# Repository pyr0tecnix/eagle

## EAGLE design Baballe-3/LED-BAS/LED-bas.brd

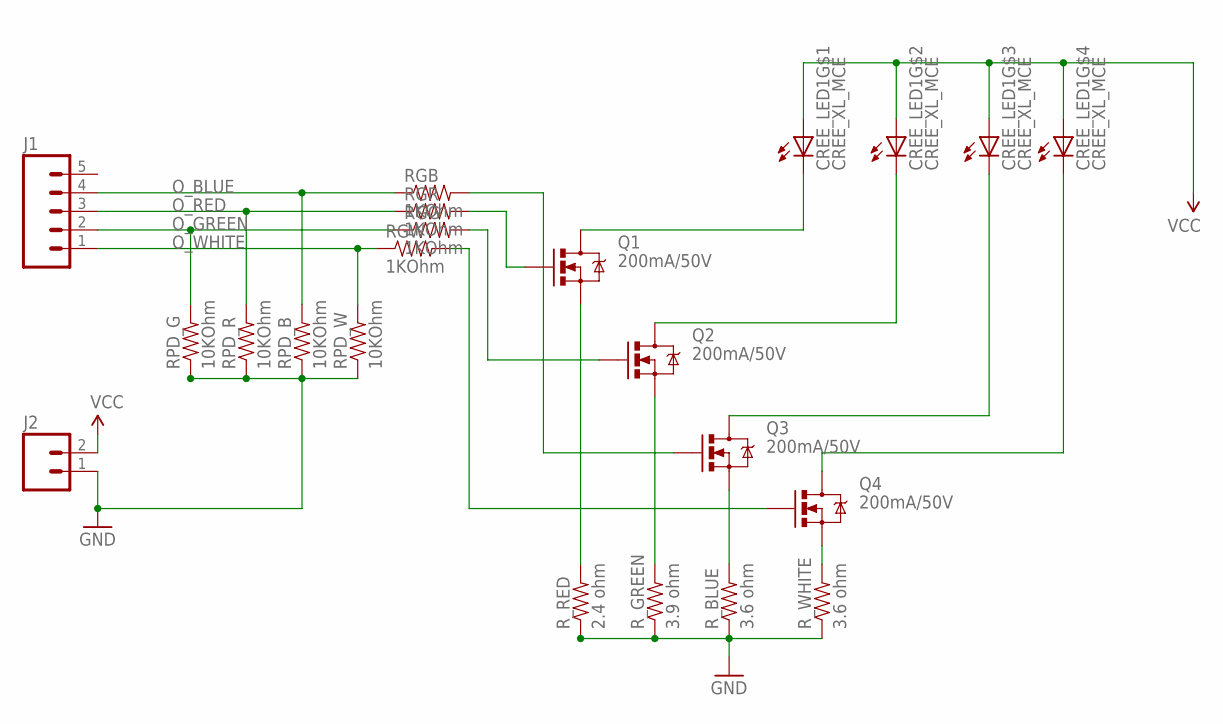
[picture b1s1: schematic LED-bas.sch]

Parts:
CREE_LED1: CREE_XL_MCE
J1: M05NO_SILK; 1X05_NO_SILK
J2: M021X02_NO_SILK; 1X02_NO_SILK
Q1, Q2, Q3, Q4: 200mA/50V; SOT23-3
RGB: 1KOhm; 0805
RGG: 1KOhm; 0805
RGR: 1KOhm; 0805
RGW: 1KOhm; 0805
RPD_B: 10KOhm; 0805
RPD_G: 10KOhm; 0805
RPD_R: 10KOhm; 0805
RPD_W: 10KOhm; 0805
R_BLUE: 3.6 ohm; 0805
R_GREEN: 3.9 ohm; 0805
R_RED: 2.4 ohm; 0805
R_WHITE: 3.6 ohm; 0805

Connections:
GND: J2.1, RPD_B.1, RPD_G.1, RPD_R.1, RPD_W.1, R_BLUE.1, R_GREEN.1, R_RED.1, R_WHITE.1
unnamed: Q3.2 (S), R_BLUE.2
unnamed: Q2.2 (S), R_GREEN.2
unnamed: Q1.2 (S), R_RED.2
unnamed: Q2.1 (G), RGG.2
unnamed: Q1.1 (G), RGR.2
unnamed: Q3.1 (G), RGB.2
unnamed: Q4.2 (S), R_WHITE.2
unnamed: CREE_LED1.6 (C), Q3.3 (D)
unnamed: CREE_LED1.8 (C), Q1.3 (D)
unnamed: CREE_LED1.7 (C), Q2.3 (D)
unnamed: Q4.1 (G), RGW.2
unnamed: CREE_LED1.5 (C), Q4.3 (D)
O_BLUE: J1.4, RGB.1, RPD_B.2
O_GREEN: J1.2, RGG.1, RPD_G.2
O_RED: J1.3, RGR.1, RPD_R.2
O_WHITE: J1.1, RGW.1, RPD_W.2
VCC: CREE_LED1.1 (A), CREE_LED1.2 (A), CREE_LED1.3 (A), CREE_LED1.4 (A), J2.2

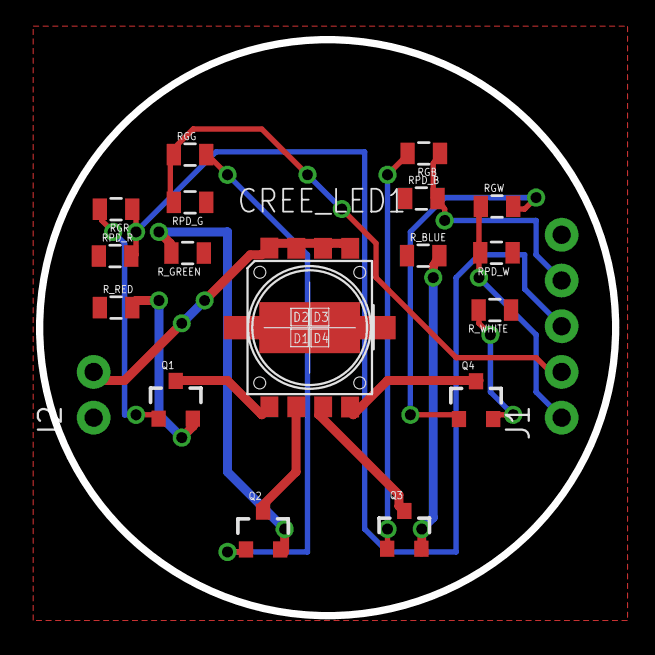
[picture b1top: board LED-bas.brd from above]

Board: 2 copper layers, 32.0 x 32.0 mm, 19 parts (0 on the bottom side), 18 nets.

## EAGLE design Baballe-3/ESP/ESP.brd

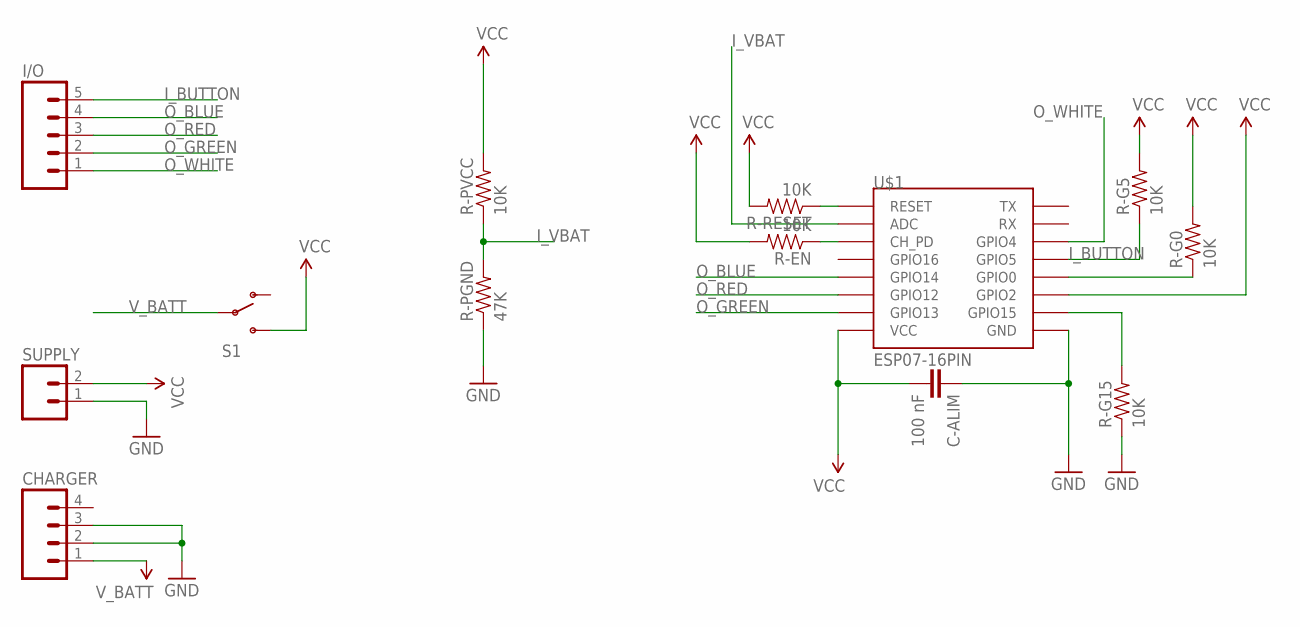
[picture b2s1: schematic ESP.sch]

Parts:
C-ALIM: 100 nF; 0805
CHARGER: M04NO_SILK_ALL_ROUND; 1X04_NO_SILK_ALL_ROUND
I/O: M05NO_SILK; 1X05_NO_SILK
R-EN: 10K; 0805
R-G0, R-G5, R-G15: 10K; 0805
R-PGND: 47K; 0805
R-PVCC: 10K; 0805
R-RESET: 10K; 0805
S1: SWITCH-SPDTSMD2; SWITCH-SPDT-SMD
SUPPLY: M021X02_NO_SILK; 1X02_NO_SILK
U$1: ESP07-16PIN

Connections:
GND: C-ALIM.1, CHARGER.2, CHARGER.3, R-G15.1, R-PGND.1, SUPPLY.1, U$1.GND
I_BUTTON: I/O.5, R-G5.1, U$1.GPIO5
I_VBAT: R-PGND.2, R-PVCC.1, U$1.ADC
unnamed: R-G15.2, U$1.GPIO15
unnamed: R-G0.1, U$1.GPIO0
unnamed: R-RESET.1, U$1.REST (RESET)
unnamed: R-EN.1, U$1.CH_PD
O_BLUE: I/O.4, U$1.GPIO14
O_GREEN: I/O.2, U$1.GPIO13
O_RED: I/O.3, U$1.GPIO12
O_WHITE: I/O.1, U$1.GPIO4
VCC: C-ALIM.2, R-EN.2, R-G0.2, R-G5.2, R-PVCC.2, R-RESET.2, S1.3 (S), SUPPLY.2, U$1.GPIO2, U$1.VCC
V_BATT: CHARGER.1, S1.2

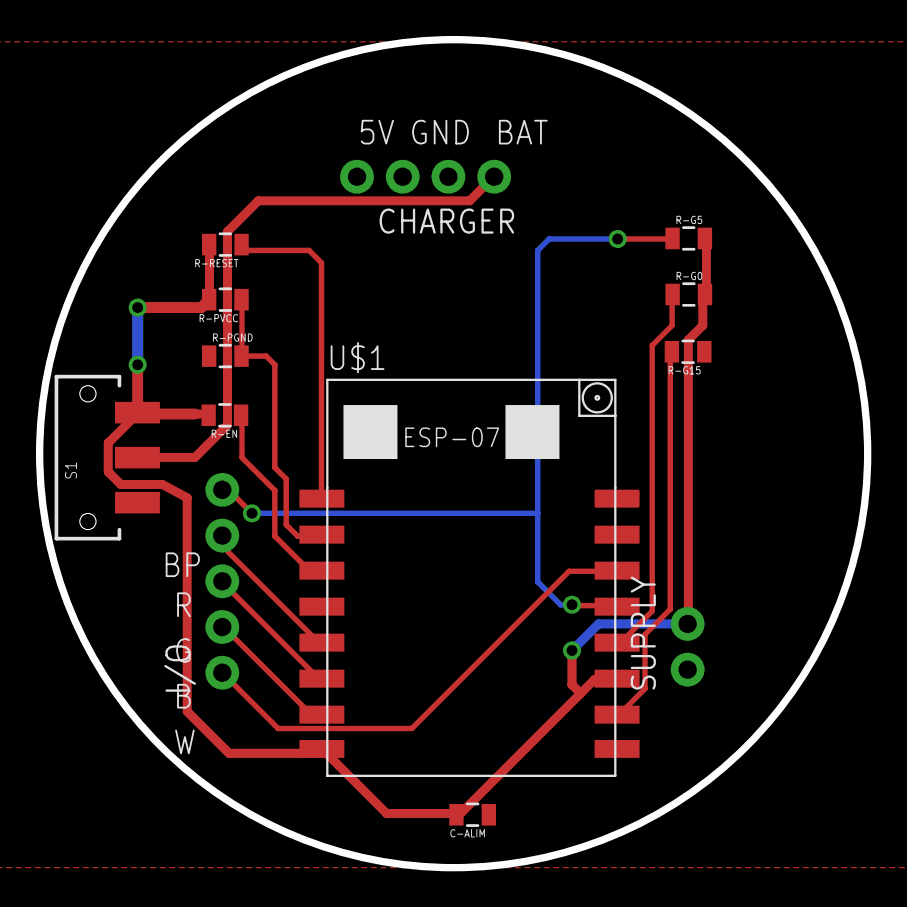
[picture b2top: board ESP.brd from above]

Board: 2 copper layers, 46.0 x 46.0 mm, 13 parts (0 on the bottom side), 13 nets.

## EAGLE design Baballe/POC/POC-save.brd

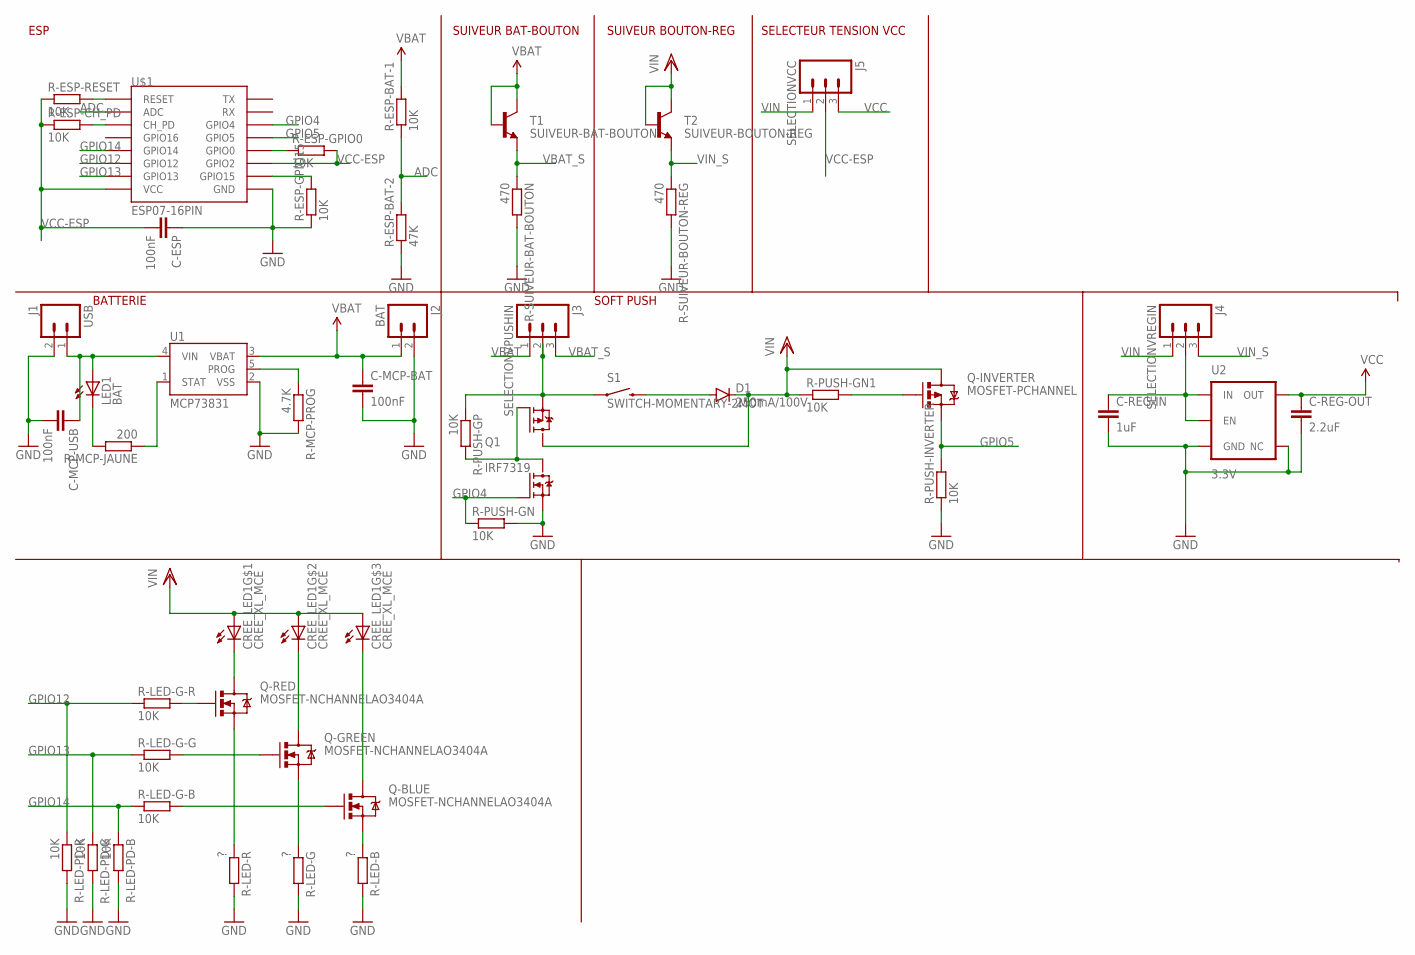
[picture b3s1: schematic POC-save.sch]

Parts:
C-ESP: 100nF; C0805
C-MCP-BAT: 100nF; C0805
C-MCP-USB: 100nF; C0805
C-REG-IN: 1uF; C0805
C-REG-OUT: 2.2uF; C0805
CREE_LED1: CREE_XL_MCE
D1: 250mA/100V; SOD-323
J1: USB; 1X02
J2: BAT; 1X02
J3: SELECTIONVPUSHIN; 1X03
J4: SELECTIONVREGIN; 1X03
J5: SELECTIONVCC; 1X03
LED1: BAT; CHIPLED_0805
Q1: IRF7319; SO08-IRF
Q-BLUE: MOSFET-NCHANNELAO3404A; SOT23-3
Q-GREEN: MOSFET-NCHANNELAO3404A; SOT23-3
Q-INVERTER: MOSFET-PCHANNEL; SOT23-3
Q-RED: MOSFET-NCHANNELAO3404A; SOT23-3
R-ESP-BAT-1: 10K; M0805
R-ESP-BAT-2: 47K; M0805
R-ESP-CH_PD: 10K; M0805
R-ESP-GPIO0, R-ESP-GPIO15: 10K; M0805
R-ESP-RESET: 10K; M0805
R-LED-B: ?; M0805
R-LED-G: ?; M0805
R-LED-G-B: 10K; M0805
R-LED-G-G: 10K; M0805
R-LED-G-R: 10K; M0805
R-LED-PD-B: 10K; M0805
R-LED-PD-G: 10K; M0805
R-LED-PD-R: 10K; M0805
R-LED-R: ?; M0805
R-MCP-JAUNE: 200; M0805
R-MCP-PROG: 4.7K; M0805
R-PUSH-GN, R-PUSH-GN1: 10K; M0805
R-PUSH-GP: 10K; M0805
R-PUSH-INVERTER: 10K; M0805
R-SUIVEUR-BAT-BOUTON: 470; M0805
R-SUIVEUR-BOUTON-REG: 470; M0805
S1: SWITCH-MOMENTARY-2MOT; TACTILE-PTH
T1: SUIVEUR-BAT-BOUTON; SOT23-3
T2: SUIVEUR-BOUTON-REG; SOT23-3
U1: MCP73831; SOT23-5
U2: 3.3V; SOT23-5
U$1: ESP07-16PIN

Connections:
ADC: R-ESP-BAT-1.1, R-ESP-BAT-2.2, U$1.ADC
GND: C-ESP.1, C-MCP-BAT.2, C-MCP-USB.2, C-REG-IN.2, C-REG-OUT.2, J1.2, J2.2, Q1.1 (N-S), R-ESP-BAT-2.1, R-ESP-GPIO15.1, R-LED-B.2, R-LED-G.2, R-LED-PD-B.2, R-LED-PD-G.2, R-LED-PD-R.2, R-LED-R.2, R-MCP-PROG.2, R-PUSH-GN.2, R-PUSH-INVERTER.1, R-SUIVEUR-BAT-BOUTON.2, R-SUIVEUR-BOUTON-REG.2, U1.2 (VSS), U2.2 (GND), U2.4 (NC), U$1.GND
GPIO4: Q1.2 (N-G), R-PUSH-GN.1, U$1.GPIO4
GPIO5: Q-INVERTER.2 (S), R-PUSH-INVERTER.2, U$1.GPIO5
GPIO12: R-LED-G-R.1, R-LED-PD-R.1, U$1.GPIO12
GPIO13: R-LED-G-G.1, R-LED-PD-G.1, U$1.GPIO13
GPIO14: R-LED-G-B.1, R-LED-PD-B.1, U$1.GPIO14
unnamed: R-ESP-GPIO15.2, U$1.GPIO15
unnamed: R-ESP-GPIO0.1, U$1.GPIO0
unnamed: R-ESP-CH_PD.2, U$1.CH_PD
unnamed: R-ESP-RESET.2, U$1.REST (RESET)
unnamed: R-MCP-PROG.1, U1.5 (PROG)
unnamed: R-MCP-JAUNE.1, U1.1 (STAT)
unnamed: LED1.C, R-MCP-JAUNE.2
unnamed: Q1.4 (P-G), Q1.7 (N-D), Q1.8 (N-D), R-PUSH-GP.2
unnamed: D1.A, S1.4 (2)
unnamed: Q-INVERTER.1 (G), R-PUSH-GN1.2
unnamed: C-REG-IN.1, J4.2, U2.1 (IN), U2.3 (EN)
unnamed: CREE_LED1.8 (C), Q-RED.3 (D)
unnamed: CREE_LED1.7 (C), Q-GREEN.3 (D)
unnamed: CREE_LED1.6 (C), Q-BLUE.3 (D)
unnamed: Q-BLUE.2 (S), R-LED-B.1
unnamed: Q-GREEN.2 (S), R-LED-G.1
unnamed: Q-RED.2 (S), R-LED-R.1
unnamed: Q-RED.1 (G), R-LED-G-R.2
unnamed: Q-GREEN.1 (G), R-LED-G-G.2
unnamed: Q-BLUE.1 (G), R-LED-G-B.2
VBAT: C-MCP-BAT.1, J2.1, J3.1, R-ESP-BAT-1.2, T1.1 (B), T1.3 (C), U1.3 (VBAT)
VBAT_S: J3.3, R-SUIVEUR-BAT-BOUTON.1, T1.2 (E)
VCC: C-REG-OUT.1, J5.3, U2.5 (OUT)
VCC-ESP: C-ESP.2, J5.2, R-ESP-CH_PD.1, R-ESP-GPIO0.2, R-ESP-RESET.1, U$1.GPIO2, U$1.VCC
VIN: CREE_LED1.1 (A), CREE_LED1.2 (A), CREE_LED1.3 (A), D1.C, J4.1, J5.1, Q1.5 (P-D), Q1.6 (P-D), Q-INVERTER.3 (D), R-PUSH-GN1.1, T2.1 (B), T2.3 (C)
VIN_S: J4.3, R-SUIVEUR-BOUTON-REG.1, T2.2 (E)
VPUSH_IN: J3.2, Q1.3 (P-S), R-PUSH-GP.1, S1.1
VUSB: C-MCP-USB.1, J1.1, LED1.A, U1.4 (VIN)

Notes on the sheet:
ESP
BATTERIE
SUIVEUR BAT-BOUTON
SOFT PUSH
SUIVEUR BOUTON-REG
SELECTEUR TENSION VCC

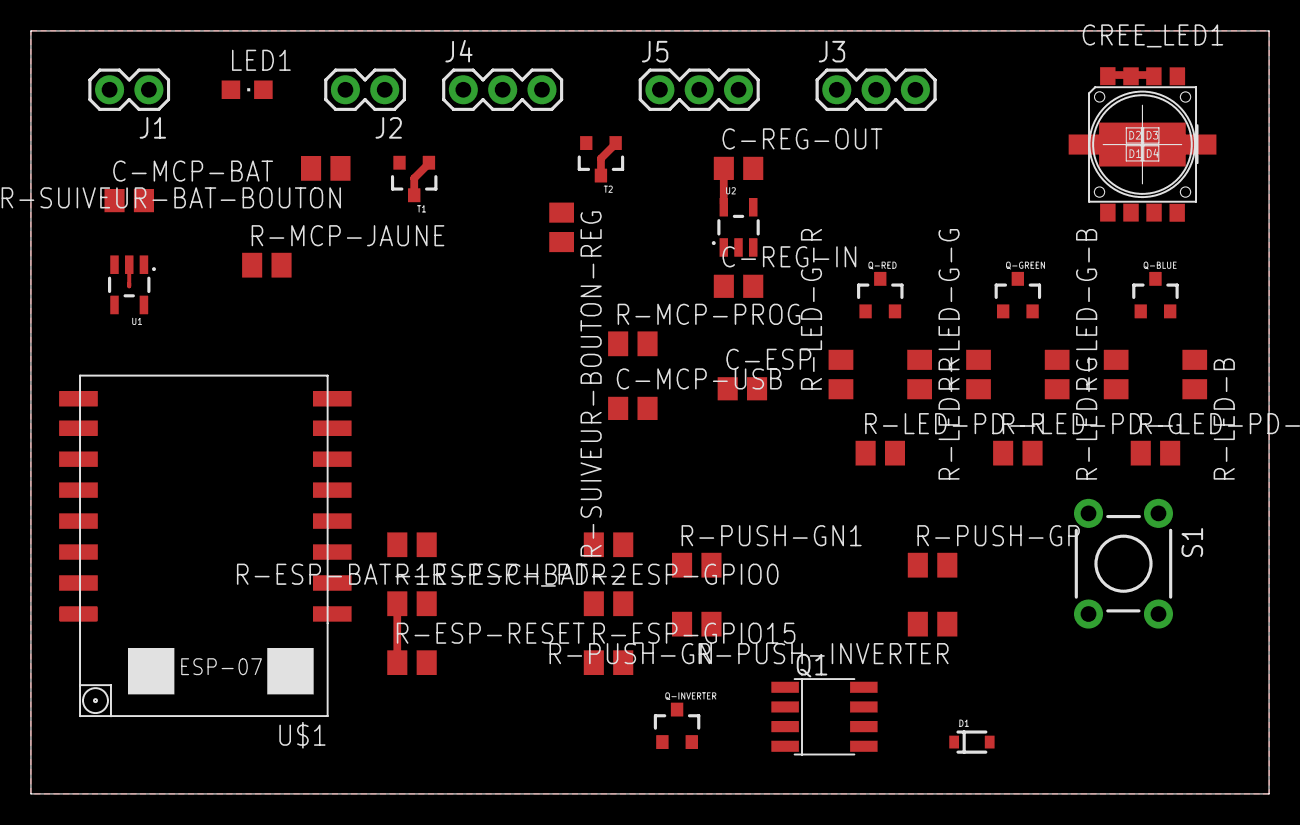
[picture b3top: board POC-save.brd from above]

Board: 2 copper layers, 80.0 x 49.3 mm, 47 parts (0 on the bottom side), 35 nets.

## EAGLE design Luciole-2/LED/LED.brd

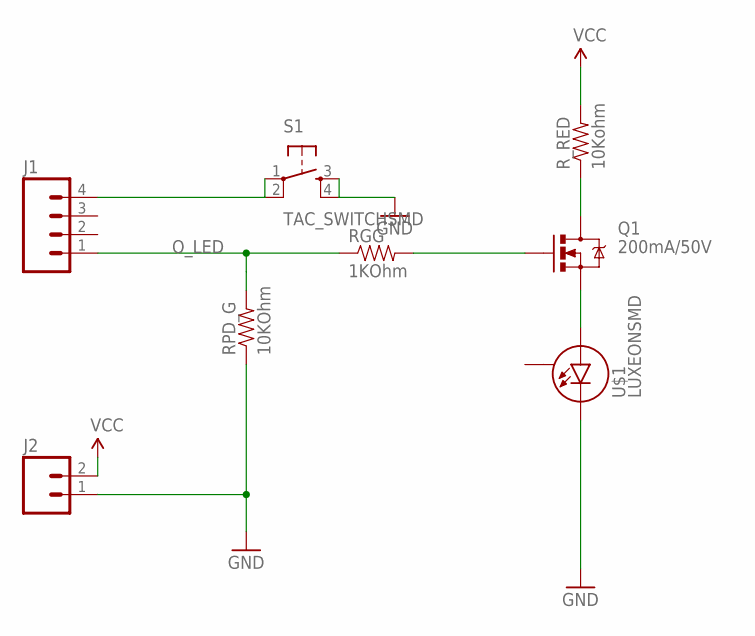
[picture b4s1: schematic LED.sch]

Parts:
J1: M04NO_SILK_ALL_ROUND; 1X04_NO_SILK_ALL_ROUND
J2: M021X02_NO_SILK; 1X02_NO_SILK
Q1: 200mA/50V; SOT23-3
RGG: 1KOhm; 0805
RPD_G: 10KOhm; 0805
R_RED: 10Kohm; 0805
S1: TAC_SWITCHSMD; TACTILE-SWITCH-SMD
U$1: LUXEONSMD; LUXEON

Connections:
GND: J2.1, S1.3, S1.4, U$1.C
unnamed: Q1.1 (G), RGG.2
unnamed: Q1.3 (D), R_RED.1
unnamed: Q1.2 (S), U$1.A
unnamed: J1.4, S1.1, S1.2
O_LED: J1.1, RGG.1, RPD_G.2
VCC: J2.2, R_RED.2

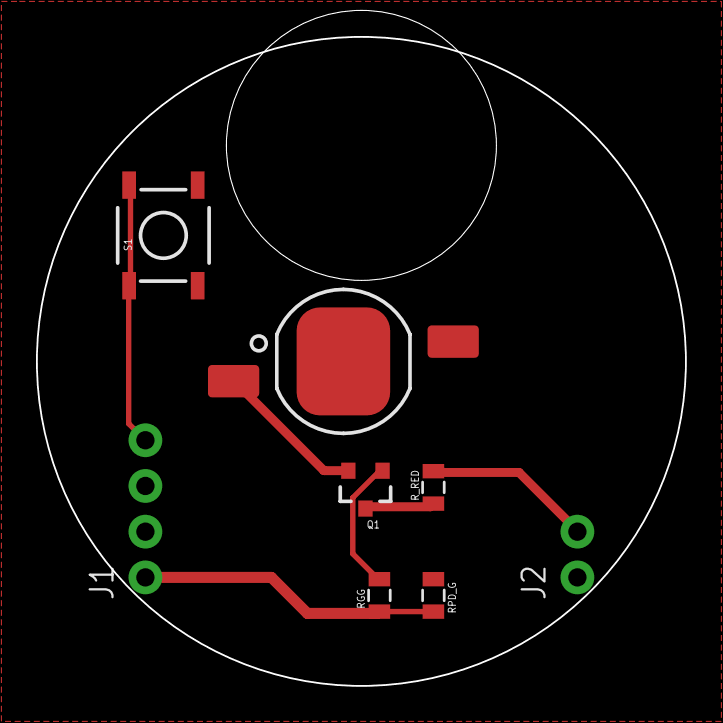
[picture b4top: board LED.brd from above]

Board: 2 copper layers, 36.1 x 36.1 mm, 8 parts (0 on the bottom side), 7 nets.

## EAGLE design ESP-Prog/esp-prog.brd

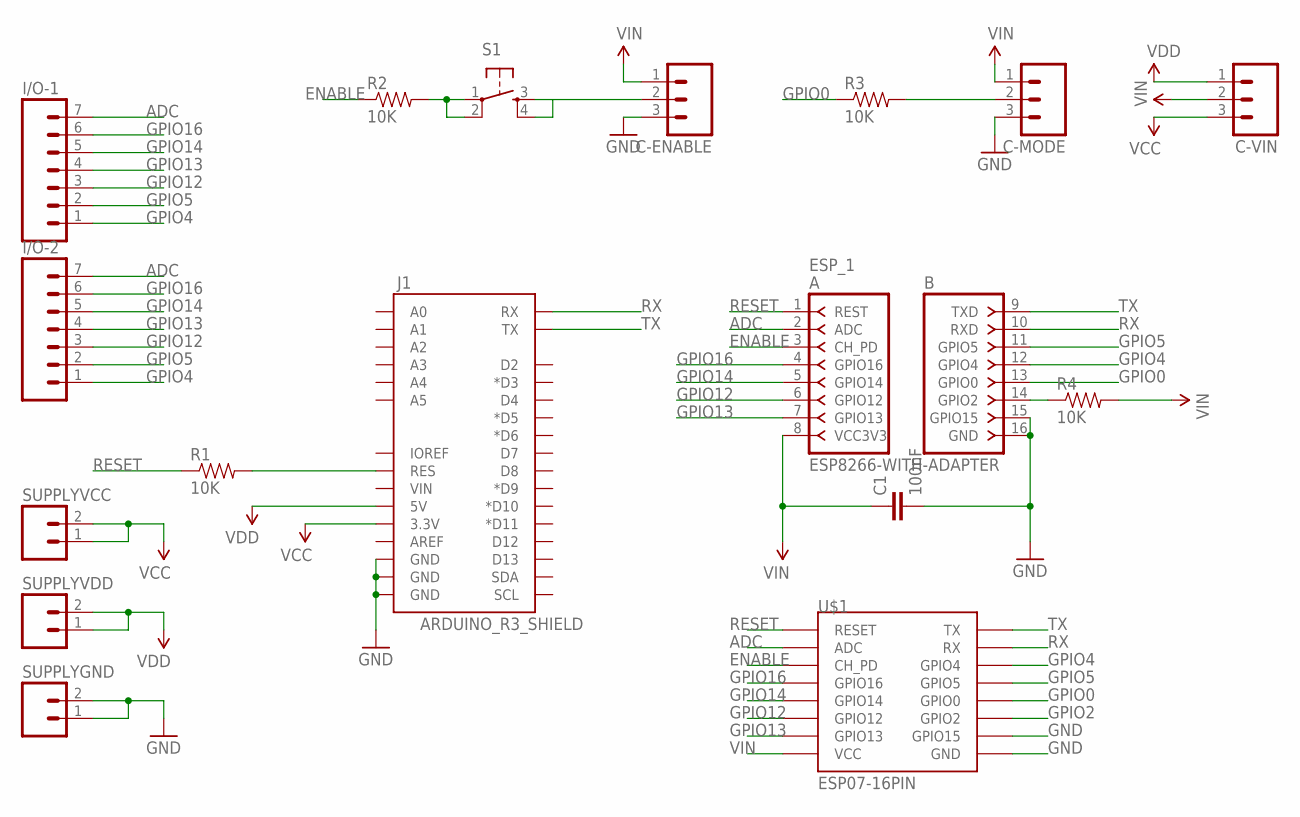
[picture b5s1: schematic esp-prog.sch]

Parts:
C1: 100nF; 0805
C-ENABLE: M031X03_NO_SILK; 1X03_NO_SILK
C-MODE: M031X03_NO_SILK; 1X03_NO_SILK
C-VIN: M031X03_NO_SILK; 1X03_NO_SILK
ESP_1: ESP8266-WITH-ADAPTER; ESP8266-ADAPTER
I/O-1, I/O-2: M07; 1X07
J1: ARDUINO_R3_SHIELD; UNO_R3_SHIELD
R1, R2, R3, R4: 10K; 0805
S1: TAC_SWITCHPTH; TACTILE-PTH
SUPPLYGND: M02PTH; 1X02
SUPPLYVCC: M02PTH; 1X02
SUPPLYVDD: M02PTH; 1X02
U$1: ESP07-16PIN

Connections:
ADC: ESP_1.2 (ADC), I/O-1.7, I/O-2.7, U$1.ADC
ENABLE: ESP_1.3 (CH_PD), R2.1, U$1.CH_PD
GND: C1.2, C-ENABLE.3, C-MODE.3, ESP_1.15 (GPIO15), ESP_1.16 (GND), J1.GND@0 (GND), J1.GND@1 (GND), J1.GND@2 (GND), SUPPLYGND.1, SUPPLYGND.2, U$1.GND, U$1.GPIO15
GPIO0: ESP_1.13 (GPIO0), R3.1, U$1.GPIO0
GPIO2: ESP_1.14 (GPIO2), R4.1, U$1.GPIO2
GPIO4: ESP_1.12 (GPIO4), I/O-1.1, I/O-2.1, U$1.GPIO4
GPIO5: ESP_1.11 (GPIO5), I/O-1.2, I/O-2.2, U$1.GPIO5
GPIO12: ESP_1.6 (GPIO12), I/O-1.3, I/O-2.3, U$1.GPIO12
GPIO13: ESP_1.7 (GPIO13), I/O-1.4, I/O-2.4, U$1.GPIO13
GPIO14: ESP_1.5 (GPIO14), I/O-1.5, I/O-2.5, U$1.GPIO14
GPIO16: ESP_1.4 (GPIO16), I/O-1.6, I/O-2.6, U$1.GPIO16
unnamed: J1.RES, R1.2
unnamed: C-MODE.2, R3.2
unnamed: R2.2, S1.1, S1.2
unnamed: C-ENABLE.2, S1.3, S1.4
RESET: ESP_1.1 (REST), R1.1, U$1.REST (RESET)
RX: ESP_1.10 (RXD), J1.RX, U$1.RX
TX: ESP_1.9 (TXD), J1.TX, U$1.TX
VBAT: C-VIN.1, J1.5V, SUPPLYVDD.1, SUPPLYVDD.2
VCC: C-VIN.3, J1.3.3V, SUPPLYVCC.1, SUPPLYVCC.2
VIN: C1.1, C-ENABLE.1, C-MODE.1, C-VIN.2, ESP_1.8 (VCC3V3), R4.2, U$1.VCC

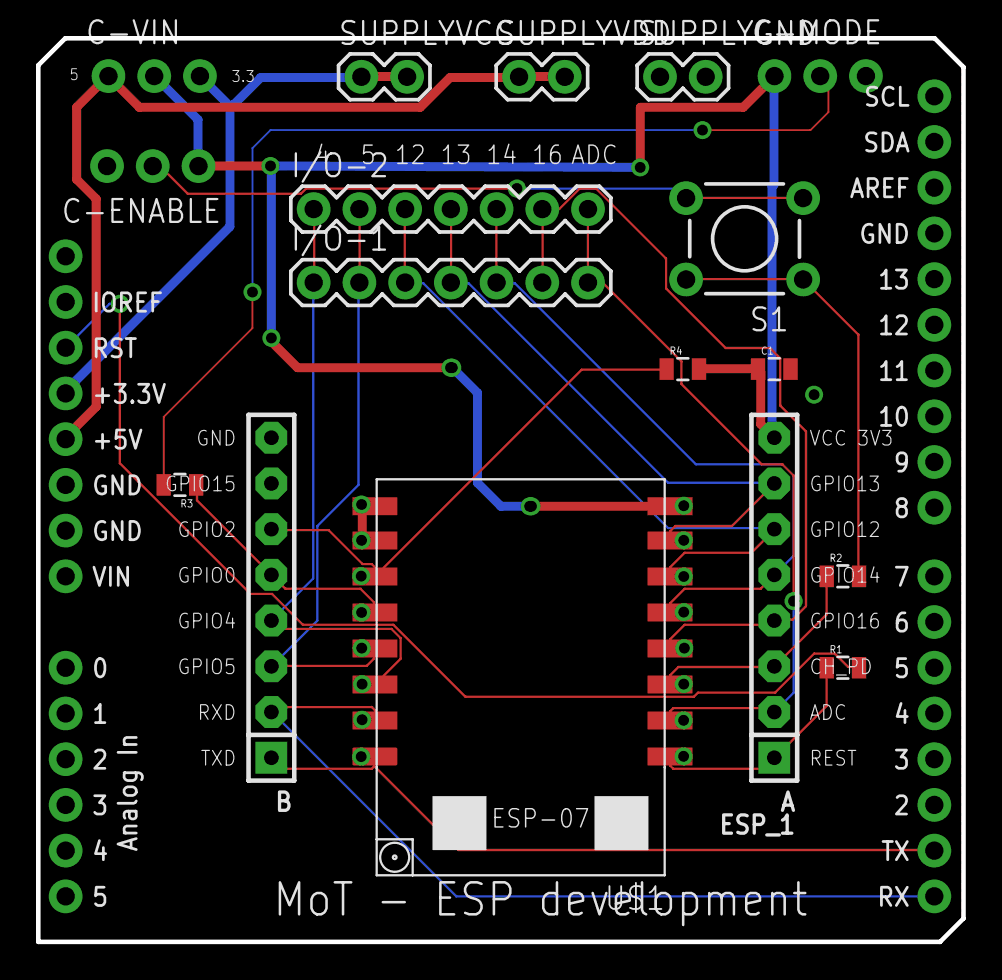
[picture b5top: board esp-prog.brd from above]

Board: 2 copper layers, 51.4 x 50.2 mm, 17 parts (0 on the bottom side), 21 nets.

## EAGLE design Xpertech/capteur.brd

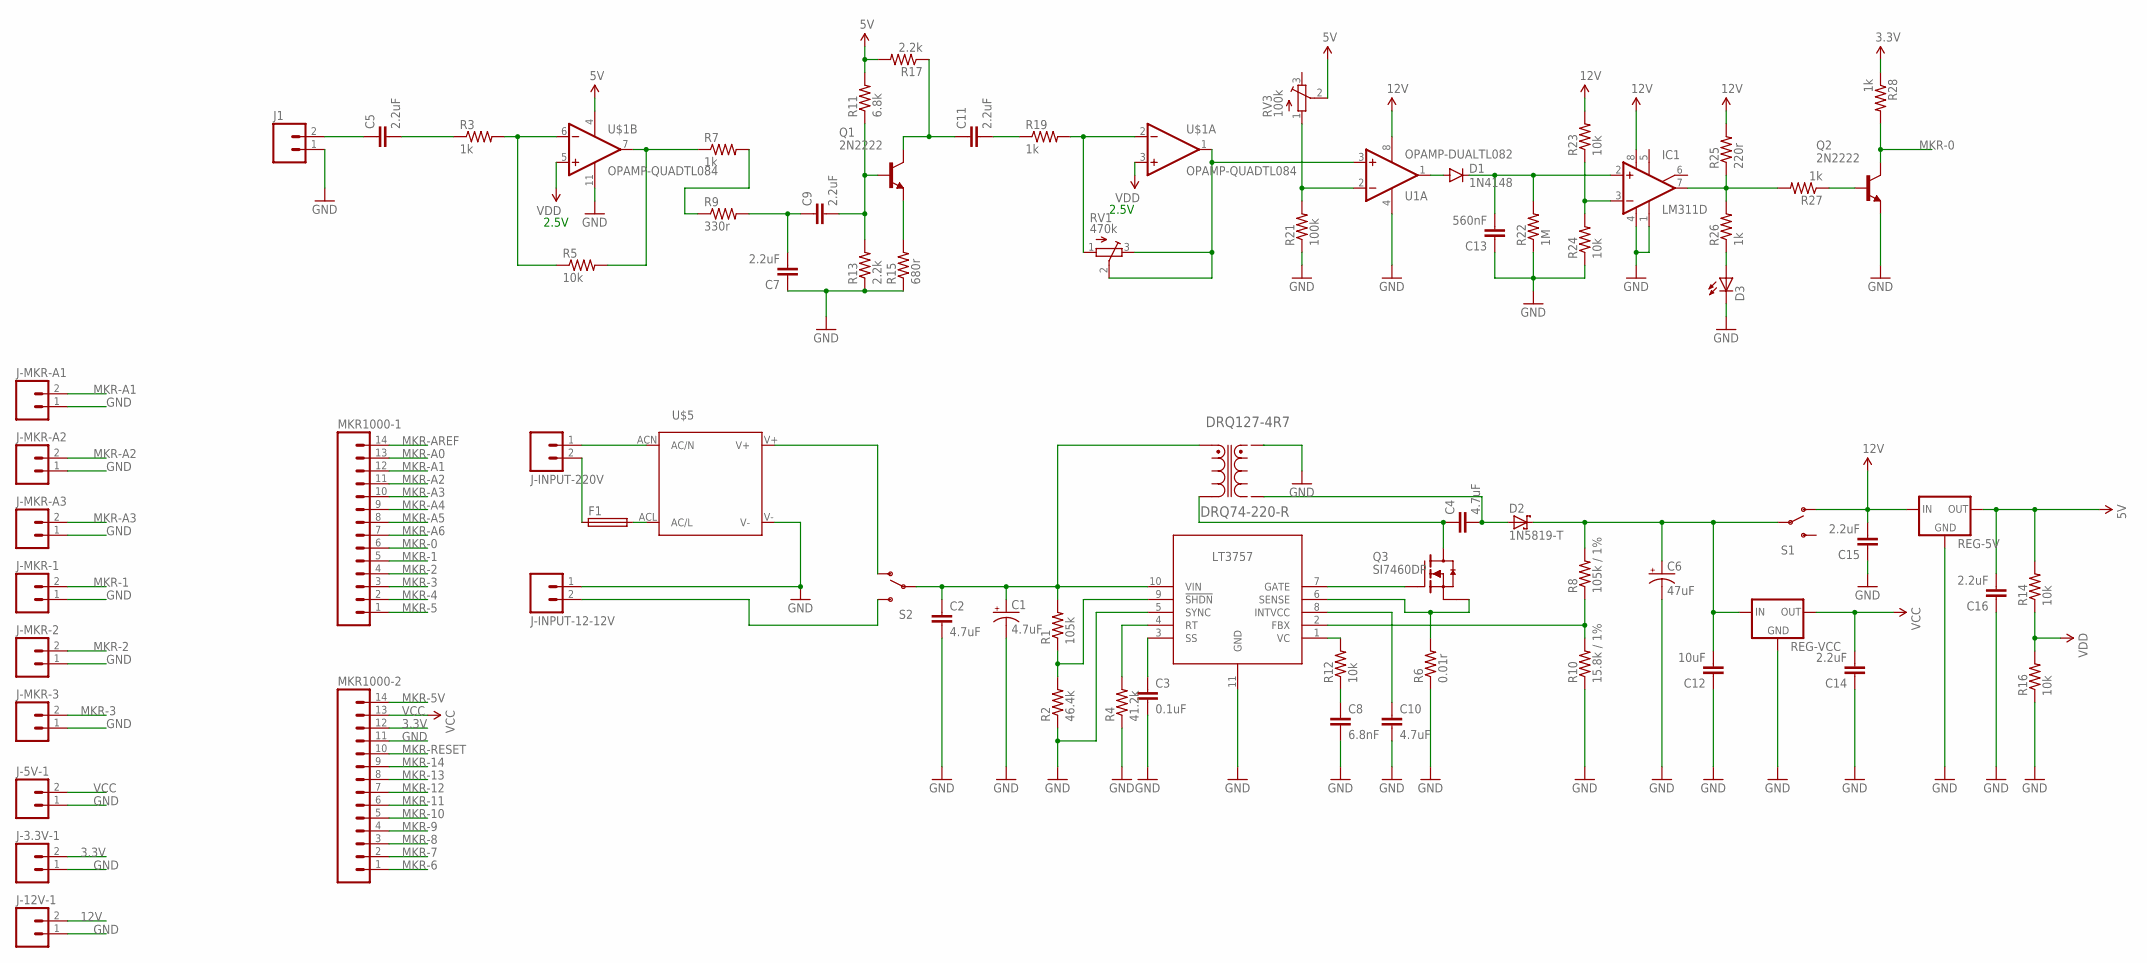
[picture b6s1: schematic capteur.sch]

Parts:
C1: 4.7uF; CPOL-RADIAL-10UF-25V
C2, C4, C10: 4.7uF; 0805
C3: 0.1uF; 0805
C5, C7, C9, C11, C14, C15, C16: 2.2uF; 0805-CAP
C6: 47uF; EIA3216
C8: 6.8nF; 0805
C12: 10uF; 0805-CAP
C13: 560nF; 0805-CAP
D1: 1N4148; SOD-123
D2: 1N5819-T; DO41-7.6
D3: LEDCHIPLED_0805; CHIPLED_0805
DRQ127-4R7: DRQ74-220-R; IND_DRQ74-220-R
F1: SH22,5A
IC1: LM311D; SO08
J1: M025MM; SCREWTERMINAL-5MM-2
J-3.3V-1, J-5V-1, J-12V-1: M025MM; SCREWTERMINAL-5MM-2
J-INPUT-12-12V, J-INPUT-220V: M025MM; SCREWTERMINAL-5MM-2
J-MKR-1, J-MKR-2, J-MKR-3: M025MM; SCREWTERMINAL-5MM-2
J-MKR-A1, J-MKR-A2, J-MKR-A3: M025MM; SCREWTERMINAL-5MM-2
MKR1000-1, MKR1000-2: M14; 1X14
Q1, Q2: 2N2222; TO18
Q3: SI7460DP; POWERPAK-SO-08
R1: 105k; 0805
R2: 46.4k; 0805
R3, R7, R19, R26, R27, R28: 1k; 0805
R4: 41.2k; 0805
R5, R12, R14, R16, R23, R24: 10k; 0805
R6: 0.01r; 2512
R8: 105k / 1%; 0805
R9: 330r; 0805
R10: 15.8k / 1%; 0805
R11: 6.8k; 0805
R13, R17: 2.2k; 0805
R15: 680r; 0805
R21: 100k; 0805
R22: 1M; 0805
R25: 220r; 0805
REG-5V: V_REG_78XXTO-92_UNTESTED; TO-92
REG-VCC: V_REG_78XXTO-92_UNTESTED; TO-92
RV1: 470k; SM-42/43W
RV3: 100k; SM-42/43W
S1, S2: SWITCH-SPDT-1; MHS122-1
U1: OPAMP-DUALTL082; DIP8
U$1: OPAMP-QUADTL084; DIP14
U$3: LT3757; 10-MSOP-EP
U$5: IRM_45/60IRM_45/60; IRM_45/60

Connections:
3.3V: J-3.3V-1.2, MKR1000-2.12, R28.1
5V: C16.2, R11.2, R14.2, R17.2, REG-5V.1 (OUT), RV3.2 (S), U$1.4 (VCC)
12V: C15.2, IC1.8 (V+), J-12V-1.2, R23.2, R25.2, REG-5V.3 (IN), S1.1 (O), U1.8 (VCC)
GND: C1.2 (-), C2.2, C3.2, C6.C (-), C7.1, C8.2, C10.2, C12.1, C13.1, C14.1, C15.1, C16.1, D3.C, DRQ127-4R7.2, IC1.1 (GND), IC1.4 (V-), J1.1, J-3.3V-1.1, J-5V-1.1, J-12V-1.1, J-INPUT-12-12V.1, J-MKR-1.1, J-MKR-2.1, J-MKR-3.1, J-MKR-A1.1, J-MKR-A2.1, J-MKR-A3.1, MKR1000-2.11, Q2.1 (E), R2.1, R4.1, R6.1, R10.1, R13.1, R15.1, R16.1, R21.1, R22.1, R24.1, REG-5V.2 (GND), REG-VCC.2 (GND), U1.4 (VEE), U$1.11 (VEE), U$3.5 (SYNC), U$3.11 (GND), U$5.V-
MKR-0: MKR1000-1.6, Q2.3 (C), R28.2
MKR-1: J-MKR-1.2, MKR1000-1.5
MKR-2: J-MKR-2.2, MKR1000-1.4
MKR-3: J-MKR-3.2, MKR1000-1.3
MKR-4: MKR1000-1.2
MKR-5: MKR1000-1.1
MKR-5V: MKR1000-2.14
MKR-6: MKR1000-2.1
MKR-7: MKR1000-2.2
MKR-8: MKR1000-2.3
MKR-9: MKR1000-2.4
MKR-10: MKR1000-2.5
MKR-11: MKR1000-2.6
MKR-12: MKR1000-2.7
MKR-13: MKR1000-2.8
MKR-14: MKR1000-2.9
MKR-A0: MKR1000-1.13
MKR-A1: J-MKR-A1.2, MKR1000-1.12
MKR-A2: J-MKR-A2.2, MKR1000-1.11
MKR-A3: J-MKR-A3.2, MKR1000-1.10
MKR-A4: MKR1000-1.9
MKR-A5: MKR1000-1.8
MKR-A6: MKR1000-1.7
MKR-AREF: MKR1000-1.14
MKR-RESET: MKR1000-2.10
unnamed: C5.2, R3.1
unnamed: R3.2, R5.1, U$1.6 (IN-)
unnamed: R5.2, R7.1, U$1.7 (OUT)
unnamed: R7.2, R9.1
unnamed: C7.2, C9.1, R9.2
unnamed: Q1.1 (E), R15.2
unnamed: C9.2, Q1.2 (B), R11.1, R13.2
unnamed: C11.1, Q1.3 (C), R17.1
unnamed: C11.2, R19.1
unnamed: R19.2, RV1.1 (A), U$1.2 (IN-)
unnamed: RV1.2 (S), RV1.3 (E), U1.3 (IN+), U$1.1 (OUT)
unnamed: D1.A, U1.1 (OUT)
unnamed: C13.2, D1.C, IC1.2 (+IN), R22.2
unnamed: IC1.7 (OUT), R25.1, R26.2, R27.2
unnamed: R21.2, RV3.1 (A), U1.2 (IN-)
unnamed: IC1.3 (-IN), R23.1, R24.2
unnamed: D3.A, R26.1
unnamed: Q2.2 (B), R27.1
unnamed: C5.1, J1.2
unnamed: Q3.3 (S3), R6.2, U$3.6 (SENSE)
unnamed: J-INPUT-220V.1, U$5.ACN (AC/N)
unnamed: J-INPUT-12-12V.2, S2.3 (S)
unnamed: S2.1 (O), U$5.V+
unnamed: C1.1 (+), C2.1, DRQ127-4R7.1, R1.2, S2.2, U$3.10 (VIN)
unnamed: Q3.4 (G), U$3.7 (GATE)
unnamed: R1.1, R2.2, U$3.9 (!SHDN)
unnamed: F1.1, J-INPUT-220V.2
unnamed: C6.A (+), C12.2, D2.C, R8.2, REG-VCC.3 (IN), S1.2
unnamed: C4.1, DRQ127-4R7.3, Q3.5-8 (D)
unnamed: C3.1, U$3.3 (SS)
unnamed: C4.2, D2.A, DRQ127-4R7.4
unnamed: R4.2, U$3.4 (RT)
unnamed: R8.1, R10.2, U$3.2 (FBX)
unnamed: R12.2, U$3.1 (VC)
unnamed: C8.1, R12.1
unnamed: F1.2, U$5.ACL (AC/L)
unnamed: C10.1, U$3.8 (INTVCC)
VBAT: R14.1, R16.2, U$1.3 (IN+), U$1.5 (IN+)
VCC: C14.2, J-5V-1.2, MKR1000-2.13, REG-VCC.1 (OUT)

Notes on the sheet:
2.5V

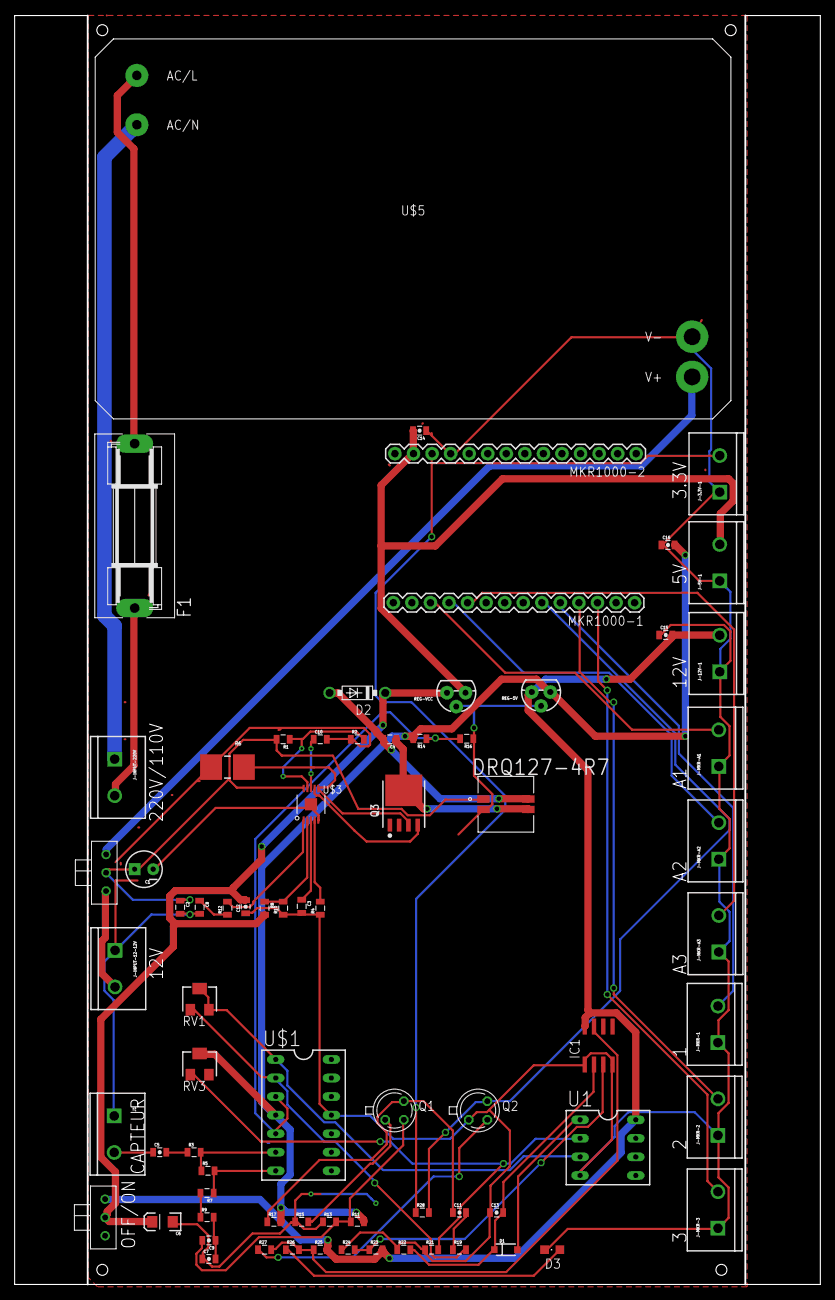
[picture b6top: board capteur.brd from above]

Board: 2 copper layers, 110.0 x 173.7 mm, 75 parts (0 on the bottom side), 50 nets.

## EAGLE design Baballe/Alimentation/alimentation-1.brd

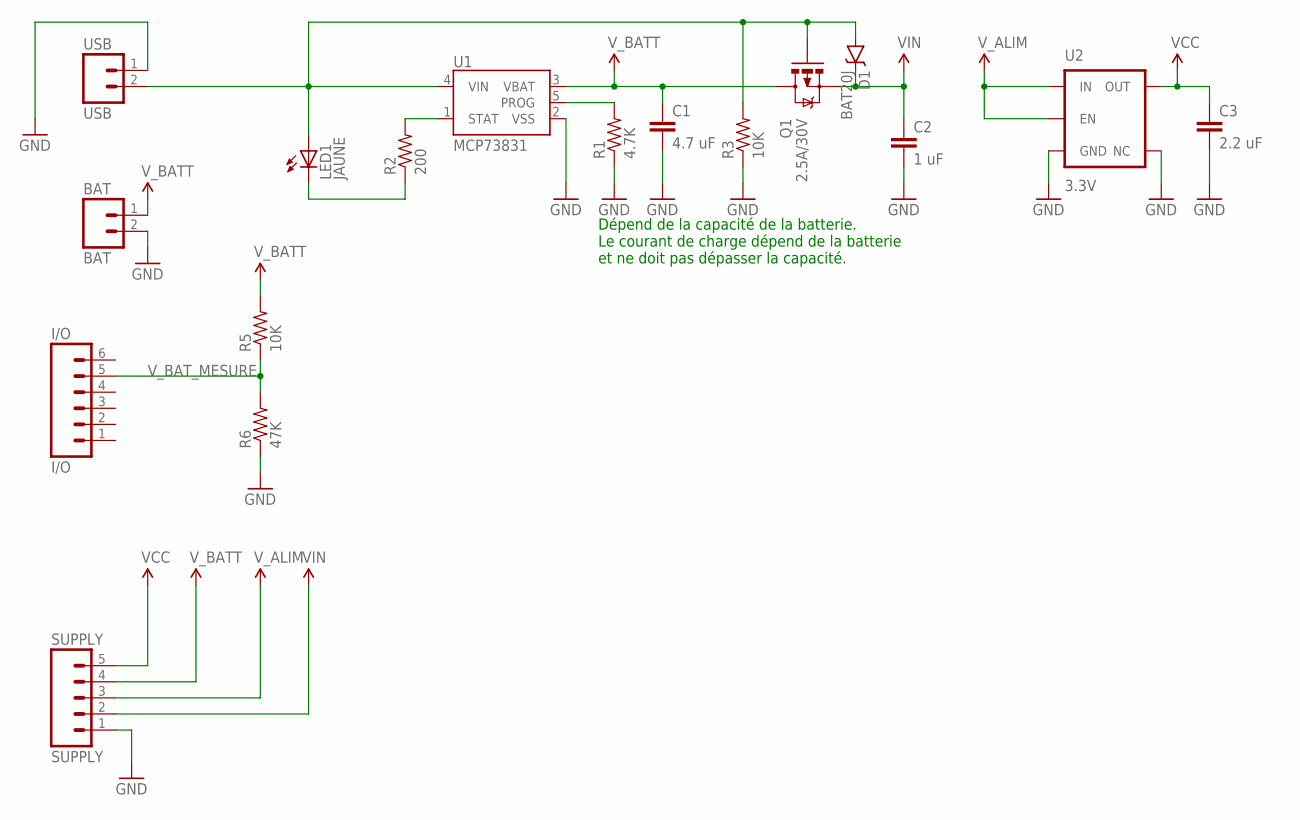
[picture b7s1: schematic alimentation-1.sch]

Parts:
BAT: BAT; 1X02_NO_SILK
C1: 4.7 uF; 0805
C2: 1 uF; 0805
C3: 2.2 uF; 0805
D1: BAT20J; SOD-323
I/O: I/O; 1X06_NO_SILK
LED1: JAUNE; LED_1206
Q1: 2.5A/30V; SOT23-3
R1: 4.7K; 0805
R2: 200; 0805
R3, R5: 10K; 0805
R6: 47K; 0805
SUPPLY: SUPPLY; 1X05_NO_SILK
U1: MCP73831; SOT23-5
U2: 3.3V; SOT23-5
USB: USB; 1X02_NO_SILK

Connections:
GND: BAT.2, C1.2, C2.2, C3.2, R1.1, R3.1, R6.1, SUPPLY.1, U1.2 (VSS), U2.2 (GND), U2.4 (NC), USB.1
unnamed: LED1.C, R2.1
unnamed: R1.2, U1.5 (PROG)
unnamed: R2.2, U1.1 (STAT)
VCC: C3.1, SUPPLY.5, U2.5 (OUT)
VCC_2: SUPPLY.3, U2.1 (IN), U2.3 (EN)
VIN: C2.1, D1.C, Q1.2 (S), SUPPLY.2
VUSB: D1.A, LED1.A, Q1.1 (G), R3.2, U1.4 (VIN), USB.2
V_BATT: BAT.1, C1.1, Q1.3 (D), R5.2, SUPPLY.4, U1.3 (VBAT)
V_BAT_MESURE: I/O.5, R5.1, R6.2

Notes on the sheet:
Dépend de la capacité de la batterie. Le courant de charge dépend de la batterie et ne doit pas dépasser la capacité.

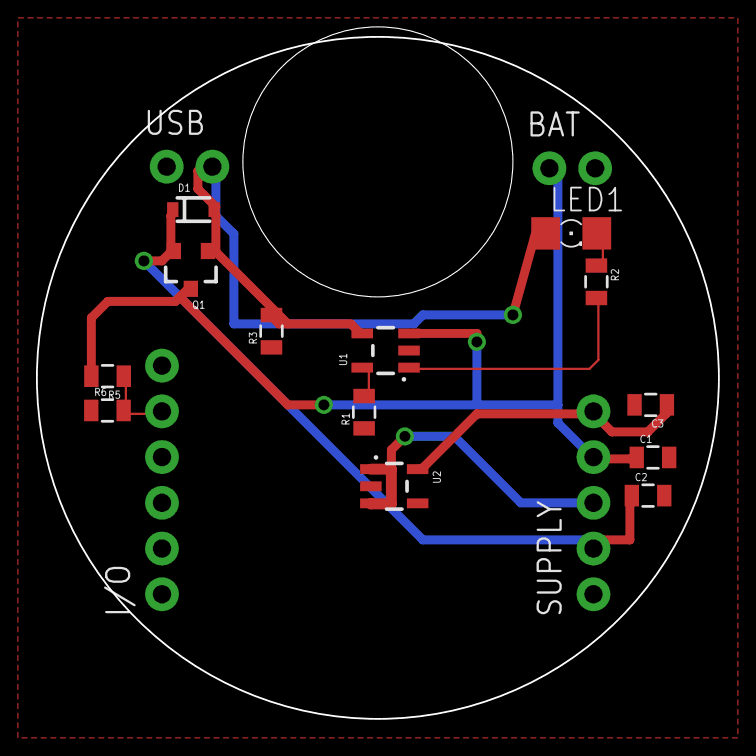
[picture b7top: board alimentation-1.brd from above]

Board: 2 copper layers, 37.9 x 37.9 mm, 17 parts (0 on the bottom side), 10 nets.

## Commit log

2016-09-18 Premier commit. Luciole en cours
2016-10-17 ESP OK ; Alimentation en cours
2016-12-04 Luciole V1 Ok ; Baballe V1 En cours
2017-03-28 Travail en cours sur la V2 de la baballe.
2017-03-31 Modification sur les modules led et alimentation
2017-04-18 V2 de la Baballe
2017-04-25 Baballe en attente de vérification finale
2017-06-03 Correction des cartes alim et boutons suite à une erreur détectée lors de l'impression
2018-09-18 Up to date
2018-11-10 Patch height error

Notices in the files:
parts and their libraries:
SparkFun-Aesthetics: Licensing: Creative Commons ShareAlike 4.0 International - https://creativecommons.org/licenses/by-sa/4.0
